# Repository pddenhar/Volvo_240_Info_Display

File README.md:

# Volvo 240 Info Display
This is a OLED dashboard module for the Volvo 240 that provides speedometer, tachometer, and battery voltage.

## PCB
The PCB layout is in KiCAD. A BOM used to purchase board components at Digikey can be found in the PCB Layout directory as well.

## Wiring
The back of the dashboard cluster has an open collector signal for the speedometer pulses (reverse engineered with help from http://cleanflametrap.com/speedo.html). This already has a 12V pullup on it, so all you need to do is connect a lead to the output.

The tachometer signal can be connected to the red and white wire present behind the gauge cluster (not connected in 240s without a tach from the factory).

12V Power and ground can be spliced into the 3-pin power cable for the gauge cluster. 

## Code
The Arduino code is compiled for the ATtiny84. You will need the ATTinyCore board library.

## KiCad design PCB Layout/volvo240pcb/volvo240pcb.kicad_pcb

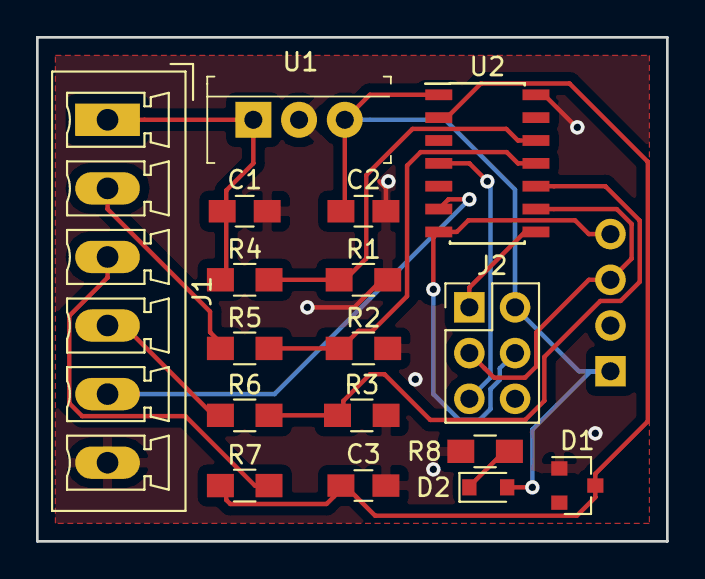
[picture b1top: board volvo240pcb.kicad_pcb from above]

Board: 2 copper layers, 35.0 x 28.0 mm, 18 parts (1 on the bottom side), 16 nets.

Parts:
C1: 0.33u; C_0805_HandSoldering
C2: 0.1u; C_0805_HandSoldering
C3: 1000p; C_0805_HandSoldering
D1: BZX84Cxx; D_SOT-23_ANK
D2: PWR; D_0805
J1: 15EDGK-3.81-05P; PhoenixContact_MCV_1,5_6-G-3.81_1x06_P3.81mm_Vertical
J2: ISP; PinHeader_2x03_P2.54mm_Vertical
J3: Display; PinHeader_1x04_P2.54mm_Vertical
R1, R2, R3: 10k; R_0805_HandSoldering
R4, R5, R6: 25k; R_0805_HandSoldering
R7: 20k; R_0805_HandSoldering
R8: 1k; R_0805_HandSoldering
U1: L7805CV; TO-220-3
U2: ATTINY84A-PU; SOIC-14_3.9x8.7mm_P1.27mm

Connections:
+12V: C1.1, J1.1, R4.1, U1.1
GND: C1.2, C2.2, C3.2, D1.2, J1.6, J2.6, J3.2, R1.2, R2.2, R3.2, R8.1, U1.2, U2.14
MISO: J2.1, U2.8
MOSI: J2.4, J3.4, U2.7
unnamed: C3.1, D1.1, R7.1, U2.2
unnamed: D2.1, R8.2
unnamed: R1.1, R4.2, U2.12
unnamed: R2.1, R5.2, U2.11
unnamed: R3.1, R6.2, U2.10
RST: J2.5, U2.4
SCK: J2.3, J3.3, U2.9
VCC: C2.1, D2.2, J2.2, J3.1, U1.3, U2.1
brake_pedal: J1.2, R5.1
servo_out: J1.5, U2.6
speedometer: J1.4, R6.1
tachometer: J1.3, R7.2

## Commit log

2018-10-25 Add PCB layout and readme
2018-10-25 Expand readme
2018-10-25 Add Arduino code
2018-10-25 Add schematic
2018-10-26 Keep circular buffer of last 25 speed and tach measurements to average
2019-02-03 Added symbol cache
2019-02-03 Update symbol libraries
